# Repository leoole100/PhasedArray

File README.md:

# Phased Array

This project is developing a phased array using cheap (0.80€) ultrasonic (40kHz) transducers like [here](https://www.aliexpress.com/item/32294219722.html?gatewayAdapt=glo2deu&spm=a2g0o.9042311.0.0.51394c4dT7BWEK).\
The main problem is the diameter of the transducers with 1.3 &lambda; in air which is over the rule of thumb for the maximal distance between elements with 0.5 &lambda;.\
First 3D printed waveguides were researched to get the emitting apertures closer.\
This causes a large loss of power which isn't feasible.\
Therefore sparse spiral array patterns are currently researched, showing promising results.

## Motivation: Localisation of an ROV

This project is for the localisation of the ROV [SIMLASUB](http://www.github.com/simlasub) which is being build by students it the [Schüler-Forschungs-Zentrum Überlingen](https://sfz-bw.de/ueberlingen/).

For the localisation of the ROV a phased array will be mounted on a boat and a single Transducer on the ROV to simplify the electronics of the ROV.\
For simplification of the problem a line of sight between the ROV and the boat is required.

Due to relatively simple and precise depth measurement with the pressure Sensor MS5837-30BA (2mm resolution down to 300m) it is sufficient to now the direction of the ROV from the boat for calculating the relative location to the boat. And with GPS the absolute location.

Two modes of operation are currently planned:

1. scanning mode: The phased array is electronically scanned over the entire search region and the direction of the strongest signal is the direction of the ROV, because reflections lose signal strength.\
To reduce false measurements the side lobe directivity should be much lower than the main lobe directivity.

This procedure could take some time if the phased Array does the mixing of the signals in hardware, which is simpler to implement. Therefore a second mode is planned:

2. tracking mode: If an old position is already know the current position can be estimated with an EKF (extended Kalman filter) and (acceleration, gyroscope, compass and steering) data from the ROV with the MPU6000 sensor.\
Therefore the position only has to be refined. This reduces the search space dramatically to a few degrees.\
Therefore the main lobe width should be optimised. This is measured as the main lobe HPFW (half-power full-width).

Optionally the hardware could be used for a third mode:

3. imaging mode: In the future the scanning data could be used for imaging the multipath reflections.\
This would be useful for navigation with the ROV.

## Simulations

For simpler testing a phased array in air (c = 343m/s) is researched.\
This mainly done using Mathematica. The code can be found in [sim](./sim/).

For a grid Array the rule of thumb is a element spacing of less than 0.5 &lambda;.
The closest the cheap 15mm large Transducers can be spaced is 1.3 &lambda;.

To calculate the directivity the transducers were modeled as point sources sending a spherical wave and interference calculated at the far field.\
The resulting data is plotted below.
The red plot (bottom, left) shows the array geometry the plot on the right he directivity. The u,v Coordinates represent the angle. The data outside the unit circle is invalid.

The side lobe level is has a difference of 0db from the main lobe. Therefore this array cant be used for scanning.

## Waveguides

To reduce the distance between the elements 3D printed waveguides can be used. This was already researched for example [3D Imaging Method for an Air-Coupled 40 kHz Ultrasound Phased-Array, Gianni Allevato et al.](https://pub.dega-akustik.de/ICA2019/data/articles/000220.pdf) and [Airborne ultrasound phased arrays, Axel Jaeger](https://tuprints.ulb.tu-darmstadt.de/9005/7/20191016-Dissertation-Axel-Jaeger.pdf).

For researching different waveguide shapes [2D](./sim/2D/) and [3D](./sim/3D/) FEM (finite element method) simulations of the pressure field around the transducers were evaluated.\
The following image shows a plot of the data from a simple 2D [simulation](./sim/2D/single_transducer.nb).

The problem is the intensity reduction of around 15 db.

## Array geometry (in progress)

Side lobes can also be reduced by tapering the power of the elements.
This can be done electronically or mechanically by reducing the density of elements at the edges of the array like in [Sunflower Array Antenna with Adjustable Density Taper, Maria Carolina Viganó et al.](https://www.semanticscholar.org/paper/Sunflower-Array-Antenna-with-Adjustable-Density-Vigan%C3%B3-Toso/11fbf66164cc196a3323513aaaddc71ceded2d92).

This can be simplified by using a spiral array geometries. 
The spiral is given with r(&phi;) = &phi;<sup>E</sup> with the Exponent E. The points are selected with the golden angle &phi;<sub>n</sub> = n * &pi;[ 3-sqrt(5)].

Here is an example:

The results of a couple more  Tests:

| Name  | Elements |Main Lobe Directivity | Side Lobe Level |
| ------------- | ----| ------------- | ----|
| [rect 8x8](./sim/res/air/rect64.png)  | 64 | 18 dbi  | 0 dbi|
| [tri 8x8](./sim/res/air/tri17.png)  | 17 | 12 dbi  | 0 dbi|
| [spiral E=0.5](./sim/res/air/0.5Spiral32.png)  | 32 | 15 dbi  | -5 dbi|
| [spiral E=0.75](./sim/res/air/0.75Spiral32.png)  | 32 | 15 dbi  | -10 dbi|
| [spiral E=1](./sim/res/air/1.0Spiral32.png)  | 32 | 15 dbi  | -10 dbi|
| [spiral E=1.25](./sim/res/air/1.25Spiral32.png)  | 32 | 15 dbi  | -10 dbi|
| [spiral E=1](./sim/res/air/1.0Spiral08.png)  | 08 | 9 dbi  | -0.9 dbi|
| [spiral E=1](./sim/res/air/1.0Spiral12.png)  | 12 | 11 dbi  | -6 dbi|
| [spiral E=1](./sim/res/air/1.0Spiral16.png)  | 16 | 12 dbi  | -5 dbi|
| [spiral E=1](./sim/res/air/1.0Spiral32.png)  | 32 | 15 dbi  | -10 dbi|
| [spiral E=1 symmetric](./sim/res/air/1.0Spiral2Sym16.png)  | 16 | 12 dbi  | -4 dbi|
| [spiral E=1 symmetric](./sim/res/air/1.0Spiral2Sym32.png)  | 32 | 15 dbi  | -10 dbi|

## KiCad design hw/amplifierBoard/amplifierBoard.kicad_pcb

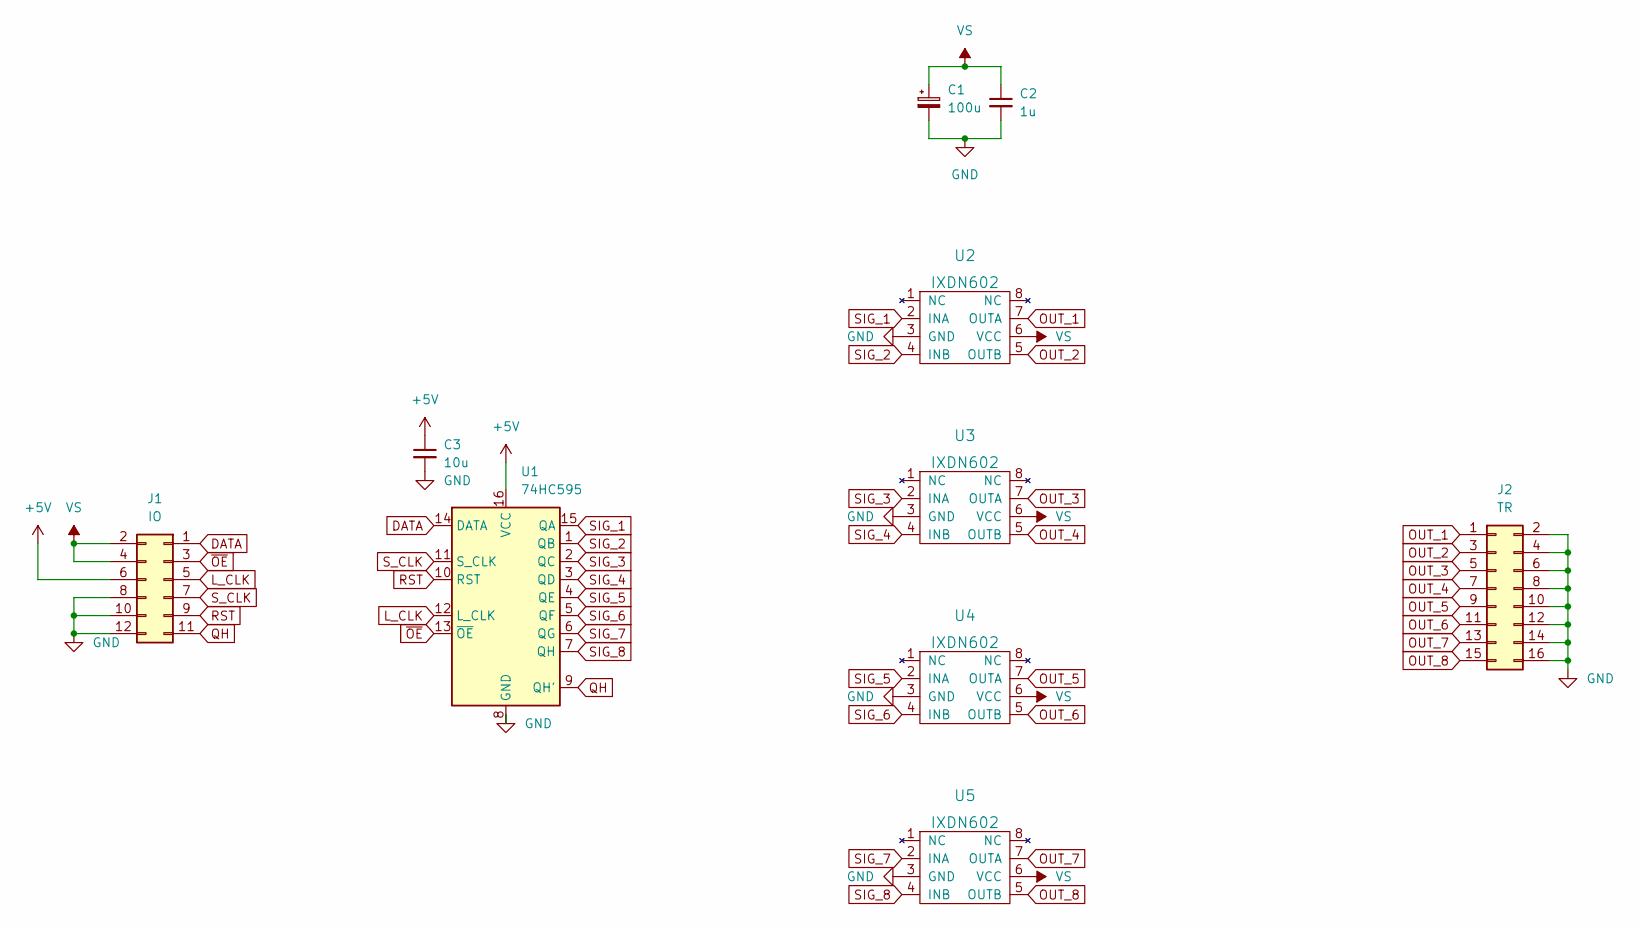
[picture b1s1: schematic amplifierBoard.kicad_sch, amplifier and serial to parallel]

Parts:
C1: 100u; CP_Radial_D8.0mm_P3.50mm; LCSC # C190967
C2: 1u; C_1206_3216Metric_Pad1.33x1.80mm_HandSolder
C3: 10u; C_1206_3216Metric_Pad1.33x1.80mm_HandSolder
J1: IO; PinHeader_2x06_P2.54mm_Horizontal
J2: TR; PinHeader_2x08_P2.54mm_Horizontal
U1: 74HC595; TSSOP-16_4.4x5mm_P0.65mm; LCSC # C110383
U2, U3, U4, U5: IXDN602; DIP-8_W7.62mm; LCSC # C426683

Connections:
+5V: C3.1, J1.6, U1.16 (VCC)
DATA: J1.1, U1.14 (DATA)
GND: C1.2, C2.2, C3.2, J1.8, J1.10, J1.12, J2.2, J2.4, J2.6, J2.8, J2.10, J2.12, J2.14, J2.16, U1.8 (GND), U2.3 (GND), U3.3 (GND), U4.3 (GND), U5.3 (GND)
L_CLK: J1.5, U1.12 (L_CLK)
OUT_1: J2.1, U2.7 (OUTA)
OUT_2: J2.3, U2.5 (OUTB)
OUT_3: J2.5, U3.7 (OUTA)
OUT_4: J2.7, U3.5 (OUTB)
OUT_5: J2.9, U4.7 (OUTA)
OUT_6: J2.11, U4.5 (OUTB)
OUT_7: J2.13, U5.7 (OUTA)
OUT_8: J2.15, U5.5 (OUTB)
QH: J1.11, U1.9 (QH')
RST: J1.9, U1.10 (RST)
SIG_1: U1.15 (QA), U2.2 (INA)
SIG_2: U1.1 (QB), U2.4 (INB)
SIG_3: U1.2 (QC), U3.2 (INA)
SIG_4: U1.3 (QD), U3.4 (INB)
SIG_5: U1.4 (QE), U4.2 (INA)
SIG_6: U1.5 (QF), U4.4 (INB)
SIG_7: U1.6 (QG), U5.2 (INA)
SIG_8: U1.7 (QH), U5.4 (INB)
S_CLK: J1.7, U1.11 (S_CLK)
VS: C1.1, C2.1, J1.2, J1.4, U2.6 (VCC), U3.6 (VCC), U4.6 (VCC), U5.6 (VCC)
~OE: J1.3, U1.13 (~OE)

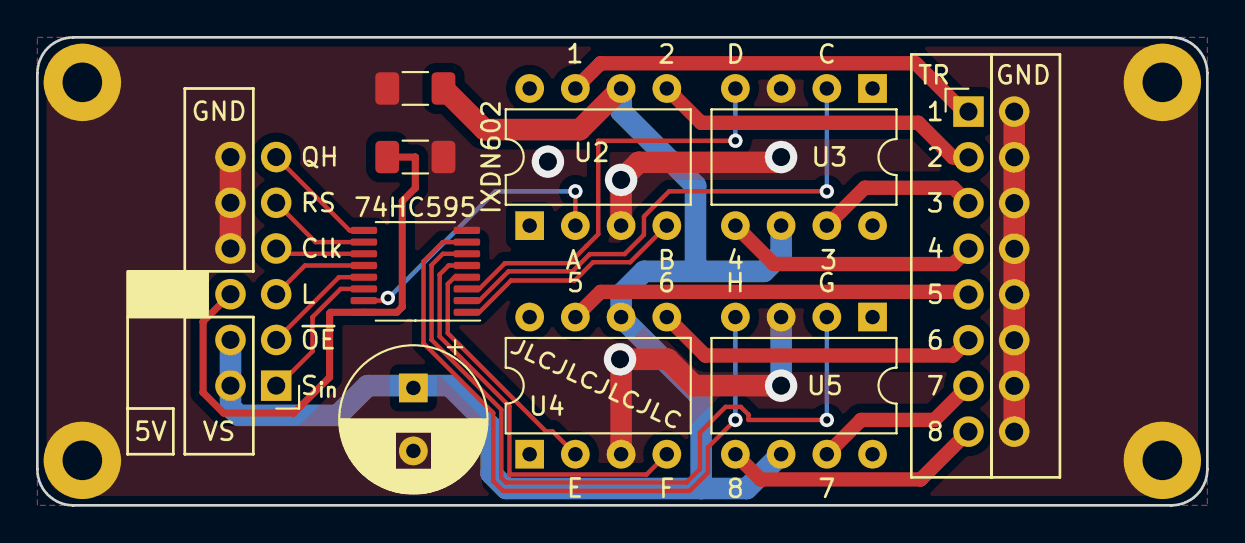
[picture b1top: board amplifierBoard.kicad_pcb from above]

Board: 2 copper layers, 65.0 x 26.0 mm, 10 parts (0 on the bottom side), 25 nets.

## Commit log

2022-02-22 added description for FEM Simulation
2022-02-22 fixed markdown formatting
2022-02-22 added pdflatex files to gitignore
2022-02-22 added simulation results
2022-02-22 fixed double main title
2022-02-23 fixed typo
2022-02-25 improved rendering of plots
2022-02-27 added to readme
2022-02-27 added short description in readme
2022-03-05 added functions to generator
2022-03-08 added recording software
2022-03-08 added nodejs gitignore
2022-03-08 added sweeping capability
